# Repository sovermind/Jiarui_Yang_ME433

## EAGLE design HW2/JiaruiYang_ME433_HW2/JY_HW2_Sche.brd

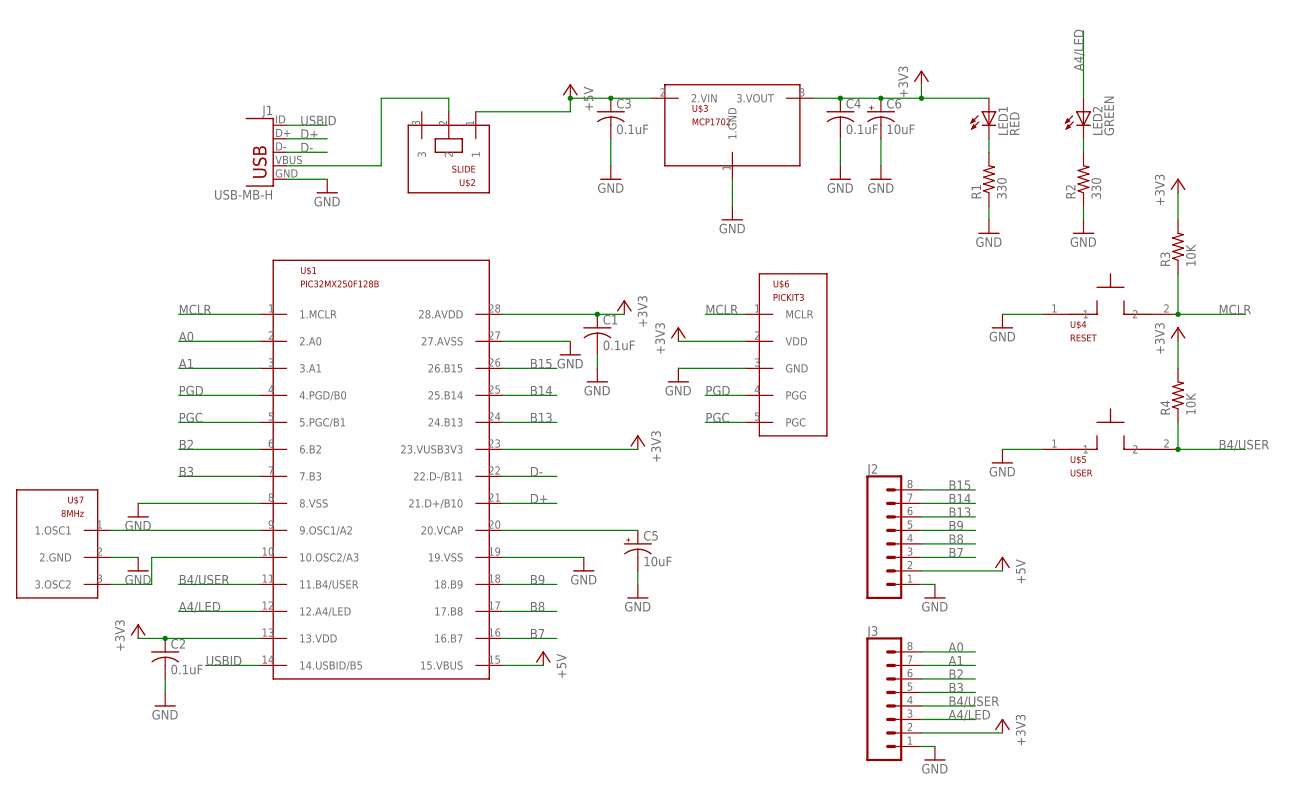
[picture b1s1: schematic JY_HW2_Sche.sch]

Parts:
C1, C2, C3, C4: 0.1uF; C025-025X050
C5, C6: 10uF; B45181B
J1: USB-MB-H
J2, J3: CONN_08"; 1X08
LED1: RED; LED3MM
LED2: GREEN; LED3MM
R1, R2: 330; 0207/10
R3, R4: 10K; 0207/10
U$1: PIC32MX250F128B; DIL28-3
U$2: SLIDE
U$3: MCP1702; TO92
U$4: RESET; PB
U$5: USER; PB
U$6: PICKIT3; 1X05
U$7: 8MHz; OSC

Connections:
+3V3: C1.1, C2.1, C4.1, C6.+, J3.2, LED1.A, R3.2, R4.2, U$1.13 (13.VDD), U$1.23 (23.VUSB3V3), U$1.28 (28.AVDD), U$3.3 (3.VOUT), U$6.2 (VDD)
+5V: C3.1, J2.2, U$1.15 (15.VBUS), U$2.1, U$3.2 (2.VIN)
A0: J3.8, U$1.2 (2.A0)
A1: J3.7, U$1.3 (3.A1)
A4/LED: J3.3, LED2.A, U$1.12 (12.A4/LED)
B2: J3.6, U$1.6 (6.B2)
B3: J3.5, U$1.7 (7.B3)
B4/USER: J3.4, R4.1, U$1.11 (11.B4/USER), U$5.2
B7: J2.3, U$1.16 (16.B7)
B8: J2.4, U$1.17 (17.B8)
B9: J2.5, U$1.18 (18.B9)
B13: J2.6, U$1.24 (24.B13)
B14: J2.7, U$1.25 (25.B14)
B15: J2.8, U$1.26 (26.B15)
D+: J1.D+, U$1.21 (21.D+/B10)
D-: J1.D-, U$1.22 (22.D-/B11)
GND: C1.2, C2.2, C3.2, C4.2, C5.-, C6.-, J1.GND, J2.1, J3.1, R1.1, R2.1, U$1.8 (8.VSS), U$1.19 (19.VSS), U$1.27 (27.AVSS), U$3.1 (1.GND), U$4.1, U$5.1, U$6.3 (GND), U$7.2 (2.GND)
MCLR: R3.1, U$1.1 (1.MCLR), U$4.2, U$6.1 (MCLR)
unnamed: J1.VBUS, U$2.2
unnamed: LED2.K (C), R2.2
unnamed: LED1.K (C), R1.2
unnamed: U$1.10 (10.OSC2/A3), U$7.3 (3.OSC2)
unnamed: U$1.9 (9.OSC1/A2), U$7.1 (1.OSC1)
unnamed: C5.+, U$1.20 (20.VCAP)
PGC: U$1.5 (5.PGC/B1), U$6.5 (PGC)
PGD: U$1.4 (4.PGD/B0), U$6.4 (PGG)
USBID: J1.ID, U$1.14 (14.USBID/B5)

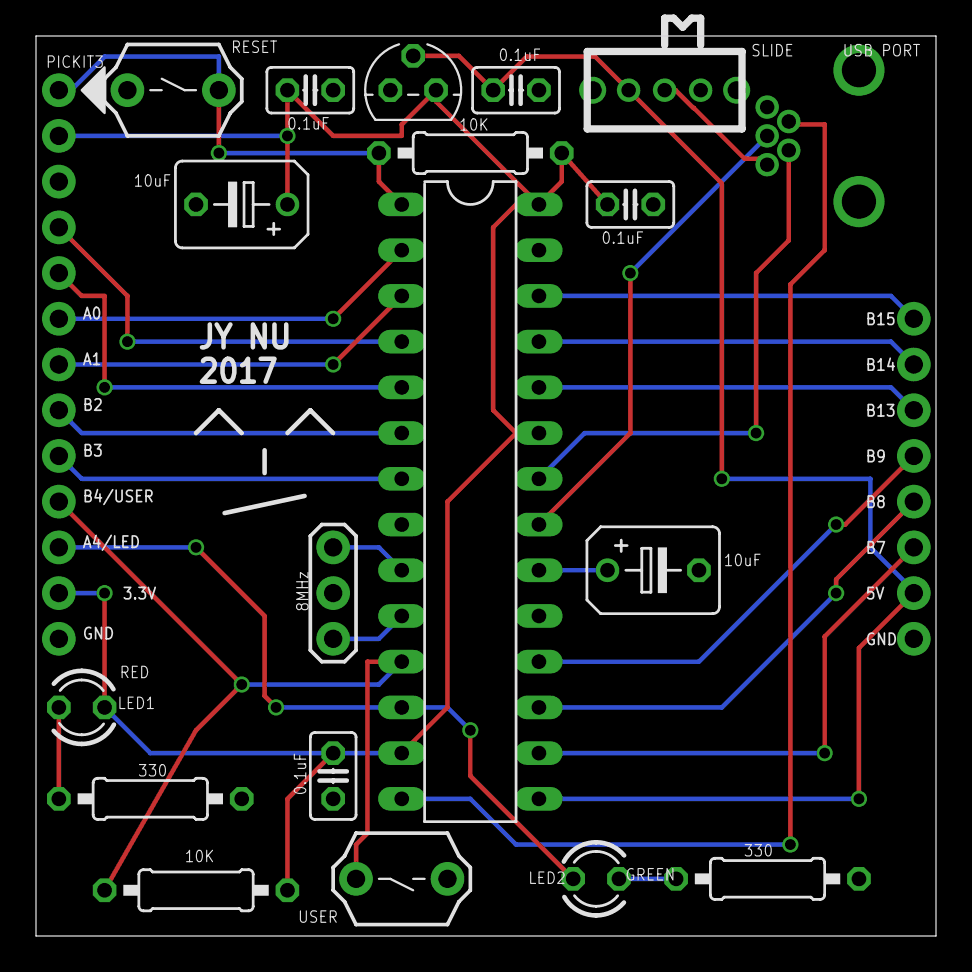
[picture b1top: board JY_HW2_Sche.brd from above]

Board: 2 copper layers, 50.0 x 50.0 mm, 22 parts (0 on the bottom side), 27 nets.

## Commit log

2017-03-29 test commit
2017-03-29 No capacitor graph
2017-03-29 With capacitor
2017-03-30 add the circuits picture
2017-03-30 create project folder
2017-03-30 set up the config varaibles
2017-03-30 fix some config variables
2017-03-30 light the LED
2017-03-30 final submission
2017-03-30 circuits drawing
2017-04-03 add lib based on video 1
2017-04-03 working on sche
2017-04-03 finish sche
2017-04-04 fix pickit error
2017-04-05 create board
2017-04-05 working on board layout
2017-04-05 finish board design version 1
2017-04-06 change lable font size
2017-04-07 cam process board
2017-04-07 some edit on board
2017-04-07 edit
2017-04-10 create new project of HW4
2017-04-10 in progress
2017-04-11 only see upper half of the signal
2017-04-11 use unsigned char
2017-04-11 all works mow
2017-04-13 start hw5 code
2017-04-13 set up the basic codes
2017-04-14 finish hw 5
2017-04-14 fix the folder location
2017-04-14 fix the led-pushbutton operating backwards
2017-04-14 start HW6
2017-04-14 set up the lcd successfully
2017-04-16 edit position of hello world
2017-04-16 finish count down of numbers
2017-04-16 add the fps count
2017-04-16 finish hw6
2017-04-19 start HW7
2017-04-19 LCD code copied from HW6
2017-04-20 who am i register working
2017-04-20 turn on accl and gyro
2017-04-21 sensor reading works
2017-04-21 pitch and roll angles from accl work now
2017-04-21 part of bar working
2017-04-21 finished HW 7
2017-04-24 start hw 8
2017-04-24 HW1 now working on harmonic
2017-04-24 Finish HW8
2017-04-25 start HW9
2017-04-26 some change
2017-04-26 add previous files
2017-04-26 press r then print
2017-04-27 timer works
2017-04-27 IMU working
2017-04-27 get rid of all LCD stuff
2017-04-27 start HW 10
2017-04-29 matlab code receive usb data
2017-04-29 matlab usb communication works
2017-04-29 IIR filter works
2017-04-30 filter edit
2017-05-01 All filters working with matlab
2017-05-02 finish HW 10
2017-05-03 start HW11
2017-05-04 mouse demo working
2017-05-04 change how MAF function works
2017-05-05 did some test, but IMU seems not working
2017-05-05 finish HW11, IMU acts wierd
2017-05-08 start HW12
2017-05-08 First app works
2017-05-09 HW12 finished
2017-05-09 small change
2017-05-09 start HW13
2017-05-09 sensitivity bar works
2017-05-09 add sensitivity text view
2017-05-11 adjust the green filter
2017-05-11 start HW14
2017-05-11 PIC works with multi char enter
2017-05-11 finish HW14
2017-05-22 HW16 3D print image
2017-05-22 design pics
2017-05-24 finish hw17
2017-06-01 start final project
2017-06-01 motor test
2017-06-02 finish motor testing HW18
2017-06-02 need test for HW19
2017-06-04 finish 19 and add vive to final project
2017-06-05 vive data works
2017-06-08 some progress
2017-06-09 finish final progject
